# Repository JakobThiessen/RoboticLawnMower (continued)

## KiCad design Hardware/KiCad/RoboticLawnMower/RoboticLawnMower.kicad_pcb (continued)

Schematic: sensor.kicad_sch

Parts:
D6, D7, D8, D9, D10, D11, D12: ESD5Zxx; D_SOD-523
J6: Coll 00; JST_XA_B03B-XASK-1_1x03_P2.50mm_Vertical
J7: Coll 01; JST_XA_B03B-XASK-1_1x03_P2.50mm_Vertical
J8: Coll 02; JST_XA_B03B-XASK-1_1x03_P2.50mm_Vertical
J19: RAIN; JST_XA_B03B-XASK-1_1x03_P2.50mm_Vertical
J20: Dist 00; JST_XA_B03B-XASK-1_1x03_P2.50mm_Vertical
J21: Dist 01; JST_XA_B03B-XASK-1_1x03_P2.50mm_Vertical
J22: Dist 02; JST_XA_B03B-XASK-1_1x03_P2.50mm_Vertical

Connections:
+3.3V: J6.1, J7.1, J8.1, J19.1, J20.1, J21.1, J22.1; also elsewhere on the board
/Sensor/DistanceSensor_00: D7.1 (K), J20.3; also elsewhere on the board
/Sensor/DistanceSensor_01: D8.1 (K), J21.3; also elsewhere on the board
/Sensor/DistanceSensor_02: D9.1 (K), J22.3; also elsewhere on the board
/Sensor/RainSensor: D6.1 (K), J19.3; also elsewhere on the board
/uC/ADC_1_IN0: D12.1 (K), J6.3; also elsewhere on the board
/uC/ADC_1_IN4: D11.1 (K), J7.3; also elsewhere on the board
/uC/ADC_1_IN8: D10.1 (K), J8.3; also elsewhere on the board
GND: D6.2 (A), D7.2 (A), D8.2 (A), D9.2 (A), D10.2 (A), D11.2 (A), D12.2 (A), J6.2, J7.2, J8.2, J19.2, J20.2, J21.2, J22.2; also elsewhere on the board

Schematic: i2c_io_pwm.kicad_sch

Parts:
C12: 100n; C_0603_1608Metric
C14: 1u; C_0603_1608Metric
R33: N.P.; R_0402_1005Metric
R34: 0R0; R_0402_1005Metric
U4: PCA9685PW; TSSOP-28_4.4x9.7mm_P0.65mm

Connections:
+3.3V: C12.1, C14.1, R33.1, U4.1 (A0), U4.2 (A1), U4.3 (A2), U4.28 (VDD); also elsewhere on the board
/Motor_M1/SCL: U4.26 (SCL); also elsewhere on the board
/Motor_M1/SDA: U4.27 (SDA); also elsewhere on the board
/PWM_CH_0: U4.6 (LED0); also elsewhere on the board
/PWM_CH_1: U4.7 (LED1); also elsewhere on the board
/PWM_CH_2: U4.8 (LED2); also elsewhere on the board
/PWM_CH_3: U4.9 (LED3); also elsewhere on the board
/PWM_CH_4: U4.10 (LED4); also elsewhere on the board
/PWM_CH_5: U4.11 (LED5); also elsewhere on the board
/PWM_CH_6: U4.12 (LED6); also elsewhere on the board
/PWM_CH_7: U4.13 (LED7); also elsewhere on the board
/PWM_CH_8: U4.15 (LED8); also elsewhere on the board
/PWM_CH_9: U4.16 (LED9); also elsewhere on the board
/PWM_CH_10: U4.17 (LED10); also elsewhere on the board
/PWM_CH_11: U4.18 (LED11)
/PWM_CH_12: U4.19 (LED12)
/PWM_CH_13: U4.20 (LED13)
/PWM_CH_14: U4.21 (LED14); also elsewhere on the board
/PWM_CH_15: U4.22 (LED15); also elsewhere on the board
/i2c_io_pwm/~PCA_9685_OE: U4.23 (~OE); also elsewhere on the board
GND: C12.2, C14.2, R34.2, U4.5 (A4), U4.14 (VSS), U4.24 (A5), U4.25 (EXTCLK); also elsewhere on the board
unnamed: R33.2, R34.1, U4.4 (A3)

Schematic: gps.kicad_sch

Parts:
D18: ESD5Zxx; D_SOD-523
J9: GPS; JST_XA_B07B-XASK-1_1x07_P2.50mm_Vertical
Q7: Si7141DP; PowerPAK_SO-8_Single
Q8: BSS123; SOT-23
R63: 1K; R_0603_1608Metric
R64: 100k; R_0603_1608Metric
R65: 1M; R_0603_1608Metric
R66: 100R; R_0603_1608Metric
U6: SRV05-4; SOT-23-6

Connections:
+3.3V: Q7.1 (S), Q7.2 (S), Q7.3 (S), R64.1; also elsewhere on the board
/GPS/GPS_MOD_EN: D18.1 (K), J9.7, R66.1; also elsewhere on the board
/GPS/GPS_PPS: J9.6, U6.1 (IO1); also elsewhere on the board
/GPS/GPS_RESET_EN: J9.5, U6.3 (IO2); also elsewhere on the board
/uC/USART_1_RX: J9.4, U6.4 (IO3); also elsewhere on the board
/uC/USART_1_TX: J9.3, U6.6 (IO4); also elsewhere on the board
GND: D18.2 (A), J9.2, Q8.2 (S), R65.2, U6.2 (VN); also elsewhere on the board
unnamed: J9.1, Q7.5 (D), U6.5 (VP)
unnamed: Q7.4 (G), R63.2, R64.2
unnamed: Q8.3 (D), R63.1
unnamed: Q8.1 (G), R65.1, R66.2

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
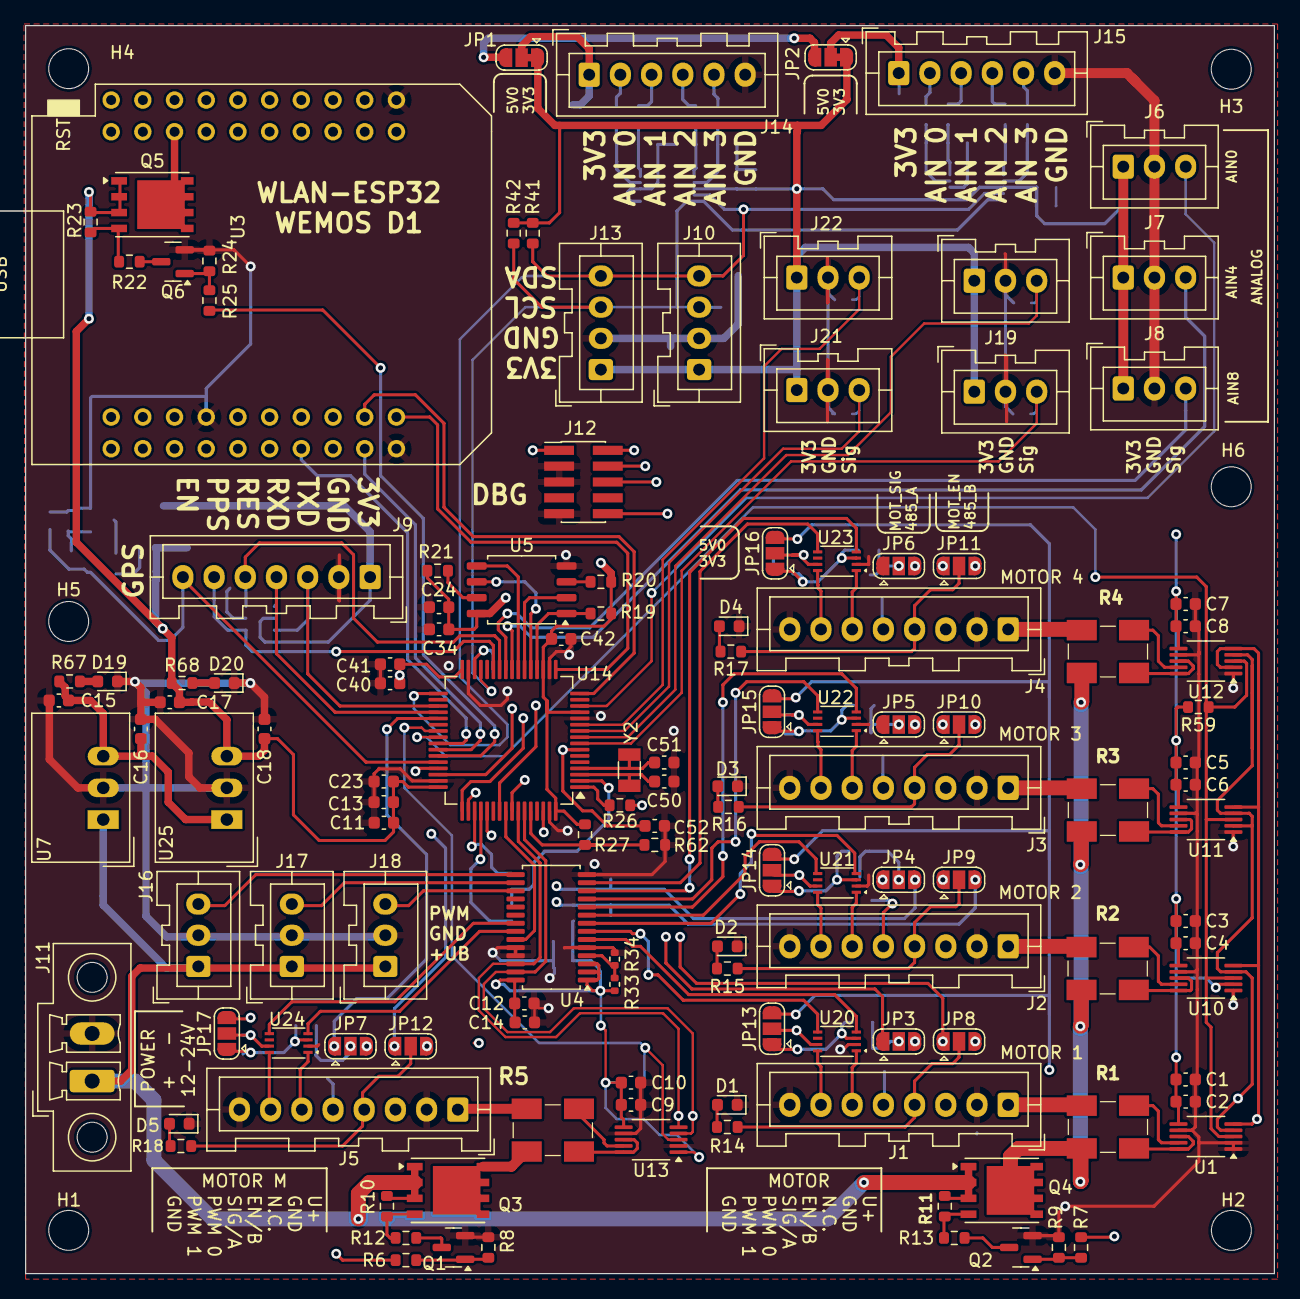
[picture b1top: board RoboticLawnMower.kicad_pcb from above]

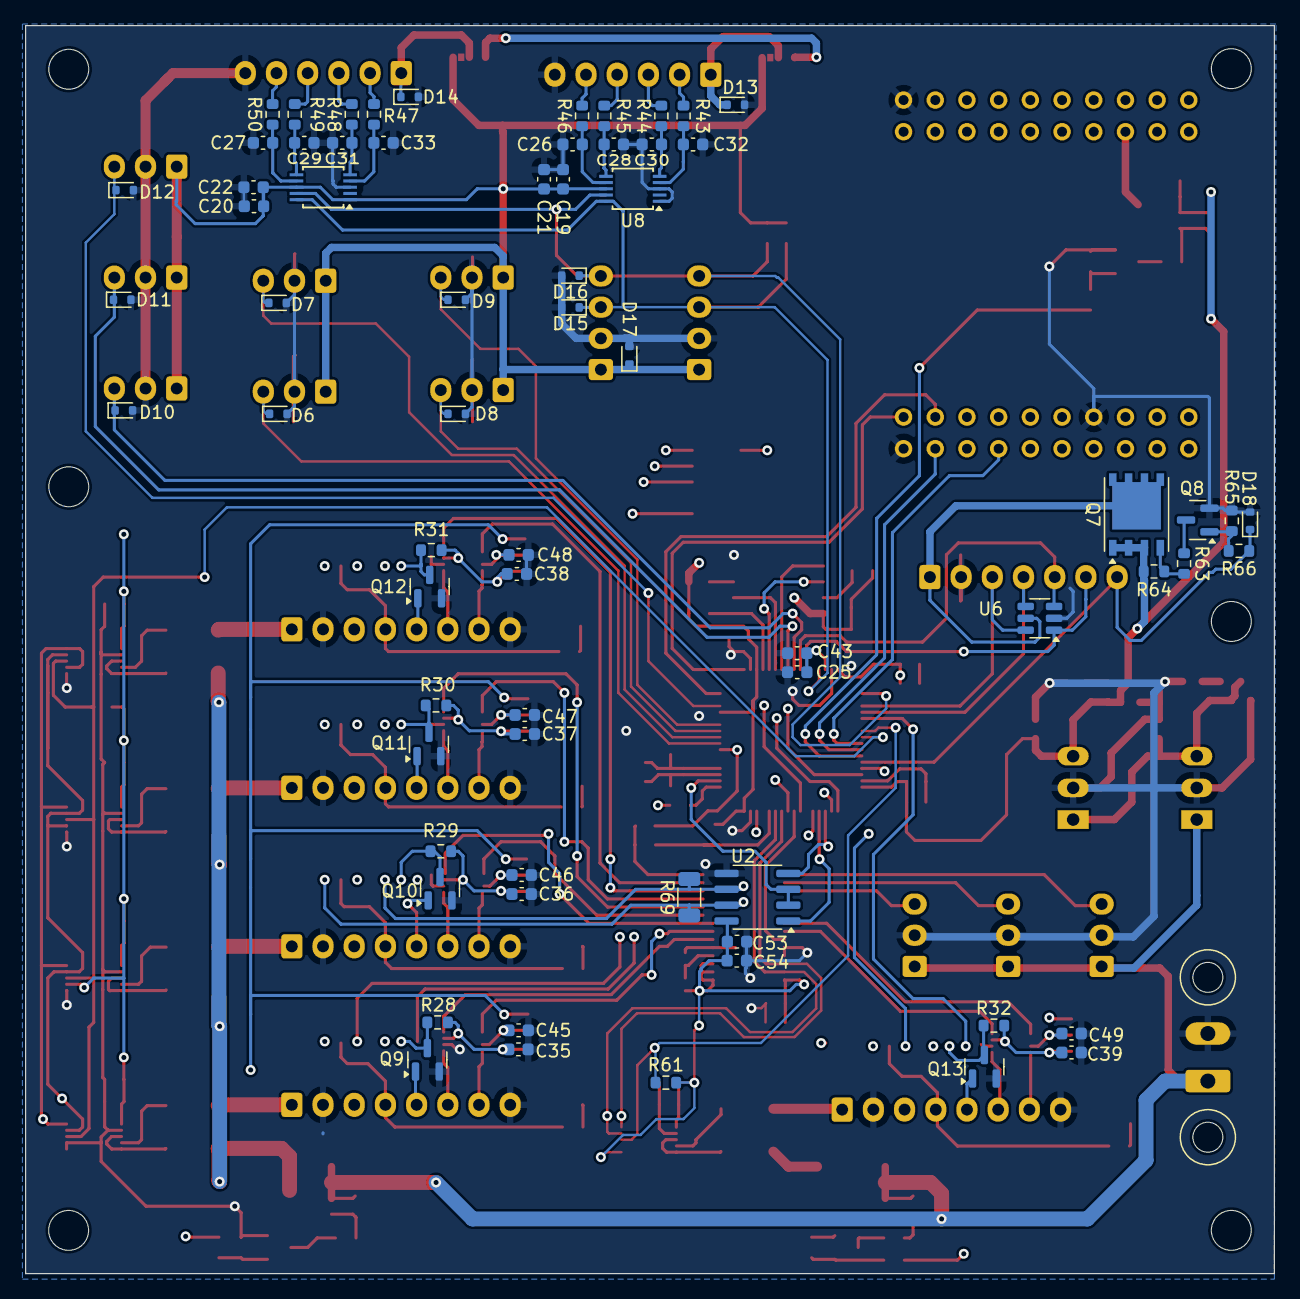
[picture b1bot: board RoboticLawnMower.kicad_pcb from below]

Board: 4 copper layers, 100.1 x 100.0 mm, 206 parts (69 on the bottom side), 153 nets.

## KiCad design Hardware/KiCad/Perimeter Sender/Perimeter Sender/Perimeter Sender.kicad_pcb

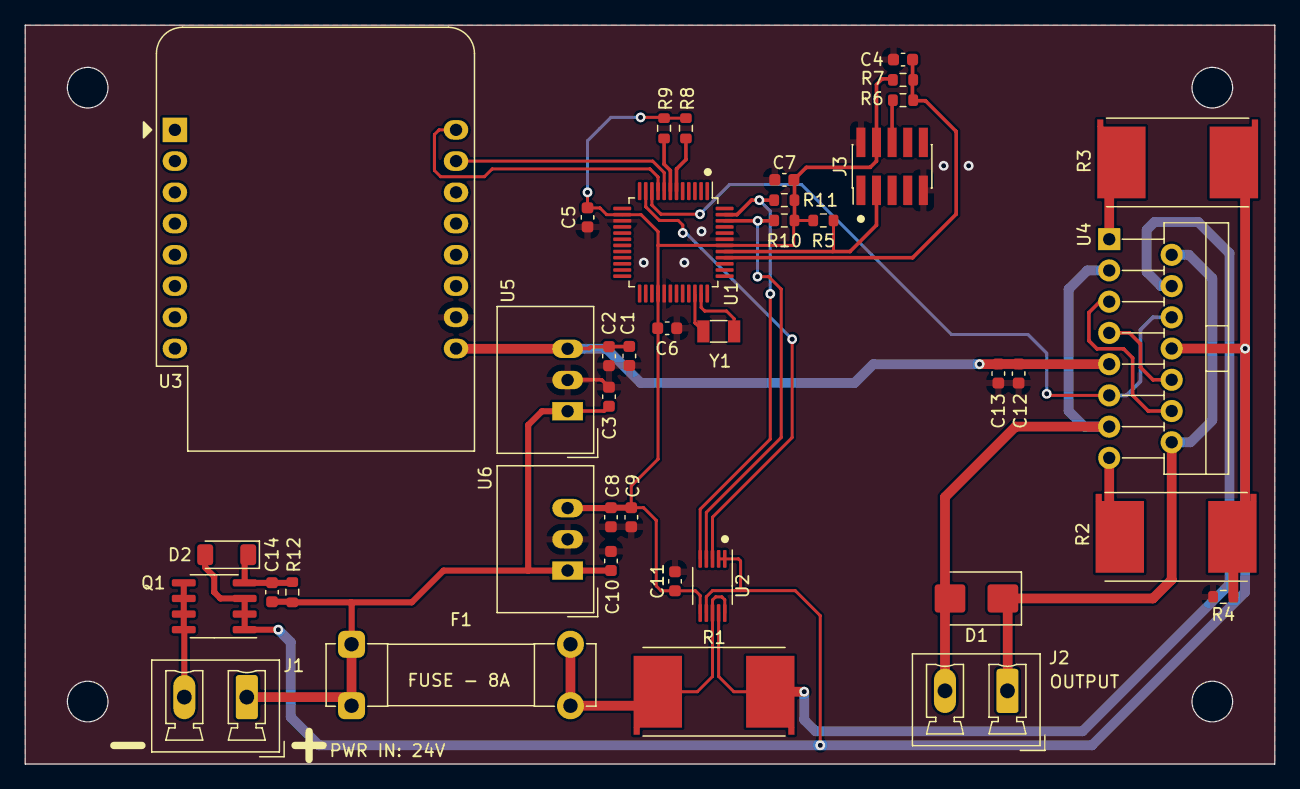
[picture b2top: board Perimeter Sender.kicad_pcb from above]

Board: 2 copper layers, 101.6 x 60.1 mm, 40 parts (0 on the bottom side), 28 nets.

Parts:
C1, C3, C8, C10: 100nF; C_0603_1608Metric
C2, C9: 4u7; C_0603_1608Metric
C4: 5p6; C_0603_1608Metric
C5, C6, C7, C11, C12: 100n; C_0603_1608Metric
C13: 1uF; C_0603_1608Metric
C14: 1nF; C_0603_1608Metric
D1: SMBJ30; D_SMB
D2: BZV55B10; D_MiniMELF
F1: 10A; Fuseholder_Clip-5x20mm_Bel_FC-203-22_Lateral_P17.80x5.00mm_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
J1, J2: Conn_01x02; PhoenixContact_MCV_1,5_2-G-5.08_1x02_P5.08mm_Vertical
J3: Conn_02x05_Row_Letter_Last; PinHeader_2x05_P1.27mm_Vertical_SMD
Q1: Si4162DY; SOIC-8_3.9x4.9mm_P1.27mm
R1, R2, R3: 0.01; R_Shunt_Vishay_WSR2_WSR3_KelvinConnection
R4: 0R0; R_0603_1608Metric
R5, R7: 47K; R_0603_1608Metric
R6: 33R; R_0603_1608Metric
R8, R9, R10, R11: 4k7; R_0603_1608Metric
R12: 10K; R_0603_1608Metric
U1: AVR128DA48x-xPT; TQFP-48_7x7mm_P0.5mm
U2: INA233; VSSOP-10_3x3mm_P0.5mm
U3: WeMos_D1_mini; WEMOS_D1_mini_light
U4: L298N; TO-220-15_P2.54x2.54mm_StaggerOdd_Lead4.58mm_Vertical
U5: TSR_1-2450; Converter_DCDC_TRACO_TSR-1_THT
U6: TSR_1-2433; Converter_DCDC_TRACO_TSR-1_THT
Y1: 32.768kHz; Crystal_SMD_3215-2Pin_3.2x1.5mm

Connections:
+3.3V: C5.1, C6.1, C7.1, C8.1, C9.1, C11.1, J3.4, R5.1, R7.1, R8.2, R9.2, R10.2, R11.2, U1.14 (VDD), U1.28 (AVDD), U1.42 (VDD), U2.6 (VS), U6.3 (Vout)
+5V: C1.1, C2.1, C12.1, C13.1, U3.9 (5V), U4.9 (Vss), U5.3 (Vout)
/POWER/POWER_IN_NEG: J1.2, Q1.5 (D), Q1.6 (D), Q1.7 (D), Q1.8 (D)
/POWER/POWER_IN_POS: C3.1, C10.1, C14.1, F1.1, J1.1, R12.1, U5.1 (Vin), U6.1 (Vin)
/POWER/POWER_NEG: D2.2 (A), Q1.1 (S), Q1.2 (S), Q1.3 (S), R2.1, R3.1, R4.1, U2.1 (A1), U2.2 (A0), U2.7 (GND), U4.8 (GND)
/POWER_OUTPUT/EN: U1.10 (PC0), U4.6 (EnA), U4.11 (EnB)
/POWER_OUTPUT/IN_1: U4.5 (IN1), U4.12 (IN4)
/POWER_OUTPUT/IN_2: U4.7 (IN2), U4.10 (IN3)
/POWER_OUTPUT/LOOP_A: D1.1 (K), J2.1, U4.2 (OUT1), U4.14 (OUT4)
/POWER_OUTPUT/LOOP_B: D1.2 (A), J2.2, U4.3 (OUT2), U4.13 (OUT3)
/POWER_OUTPUT/SCL: R11.1, U1.47 (PA3), U2.5 (SCL)
/POWER_OUTPUT/SDA: R10.1, U1.46 (PA2), U2.4 (SDA)
/POWER_OUTPUT//ALERT: U1.11 (PC1), U2.3 (~Alert)
/uC/AVR_UPDI: J3.3, R5.2, U1.41 (UPDI)
/uC/I2C_1_SCL: R9.1, U1.7 (PB3)
/uC/I2C_1_SDA: R8.1, U1.6 (PB2)
/uC/UART_3_RXD: U1.9 (PB5), U3.16 (TX)
/uC/UART_3_TXD: U1.8 (PB4), U3.15 (RX)
/uC/~AVR_RERSET: C4.1, R6.2, R7.2, U1.40 (~RESET/PF6)
GND: C1.2, C2.2, C3.2, C4.2, C5.2, C6.2, C7.2, C8.2, C9.2, C10.2, C11.2, C12.2, C13.2, J3.2, J3.9, R4.2, U1.15 (GND), U1.29 (GND), U1.43 (GND), U3.10 (GND), U5.2 (GND), U6.2 (GND)
unnamed: C14.2, D2.1 (K), Q1.4 (G), R12.2
unnamed: J3.6, R6.1
unnamed: U1.34 (XTAL32K1/PF0), Y1.2
unnamed: U1.35 (XTAL32K2/PF1), Y1.1
unnamed: F1.2, R1.1, U2.8 (Vbus), U2.10 (Vin+)
unnamed: R1.2, U2.9 (Vin-), U4.4 (Vs)
unnamed: R3.2, U4.1 (SENSE_A)
unnamed: R2.2, U4.15 (SENSE_B)

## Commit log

2022-10-18 Schaltplan hinzugefügt. Erster entwurf
2022-10-21 main_board.brd - Layout
2022-10-22 Layout
2022-10-31 layout update
2022-11-01 schaltplan und layout
2023-01-21 bild hinzugefügt.
2023-01-23 Konzept bild angepasst
2023-01-24 Systemkonzept angepasst
2023-01-25 konzept
2023-02-04 Schaltplan und Layout änderung
2023-02-06 readme angepasst
2023-02-07 readme
2023-02-08 Schaltplan & Layout Änderung
2023-02-08 readme Änderung
2023-02-11 Layout ready add gerber file
2023-02-28 kleine Änderung
2023-02-28 projekt aufgeräumt
2023-02-28 add embedded project
2023-03-01 add driver - BMM150 - INA228
2023-03-04 driver
2023-03-07 bugFix driver BMI160 BMM150
2023-03-07 bug fix bmm150 bmi160
2023-03-11 add pca9685 driver
2023-03-12 add gps/nmea driver
2023-03-19 add TMAG5273 driver add lwgps driver
2023-03-27 FreeRTOS
2023-07-30 add gps communcation on usart3
2023-07-30 save files with KiCad 7.0
2023-08-03 firmware angepassst LabVIew Projekt erstellt
2023-08-17 LAbView Projekt angepasst
2023-09-11 LabView projekt angepasst Embedded: - Treiber für VL53L1X hinzugefügt (Nicht ganz fertig)
2023-09-11 implement driver: - VL53L1X
2023-09-12 Motor L und R läuft Abstandsensor läuft Kollision läuft
2023-09-17 State Machine für den Ablauf.
2023-10-08 add perimeter sender
2024-06-02 Redesign: - Controller - I2C pinning geändert - uvm
2024-06-02 Schaltplan hinzugefügt RS485 Lib hinzugefügt
2024-06-02 hinterrad 3d model
2024-06-03 änderung
2025-04-07 change µC to STM32H573
2025-04-11 Layout fertig, Gerber-Datei muss noch erzeugt werden.
2025-04-11 Dokumentation
2025-04-14 Levelshift für MotorSignal zum µC
2025-04-14 gerberdaten erzeugt
